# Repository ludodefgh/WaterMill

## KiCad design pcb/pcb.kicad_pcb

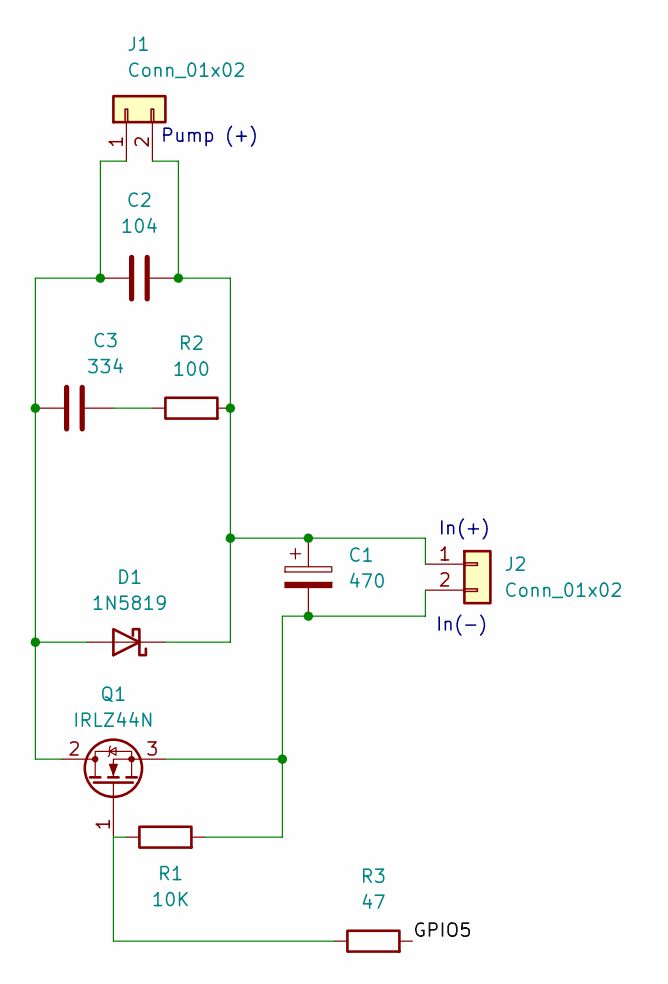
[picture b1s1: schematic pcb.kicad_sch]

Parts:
C1: 470; CP_Radial_D8.0mm_P3.50mm
C2: 104; C_Disc_D5.0mm_W2.5mm_P2.50mm
C3: 334; C_Disc_D5.0mm_W2.5mm_P2.50mm
D1: 1N5819; D_DO-41_SOD81_P10.16mm_Horizontal
J1, J2: Conn_01x02; JST_PH_B2B-PH-K_1x02_P2.00mm_Vertical
Q1: IRLZ44N; TO-220-3_Vertical
R1: 10K; R_Axial_DIN0207_L6.3mm_D2.5mm_P10.16mm_Horizontal
R2: 100; R_Axial_DIN0207_L6.3mm_D2.5mm_P10.16mm_Horizontal
R3: 47; R_Axial_DIN0207_L6.3mm_D2.5mm_P10.16mm_Horizontal

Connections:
/GPIO5: R3.2
unnamed: C3.2, R2.1
unnamed: C2.1, C3.1, D1.2 (A), J1.1, Q1.2 (D)
unnamed: C1.1, C2.2, D1.1 (K), J1.2, J2.1, R2.2
unnamed: C1.2, J2.2, Q1.3 (S), R1.2
unnamed: Q1.1 (G), R1.1, R3.1

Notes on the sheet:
Pump (+)
In(-)
In(+)

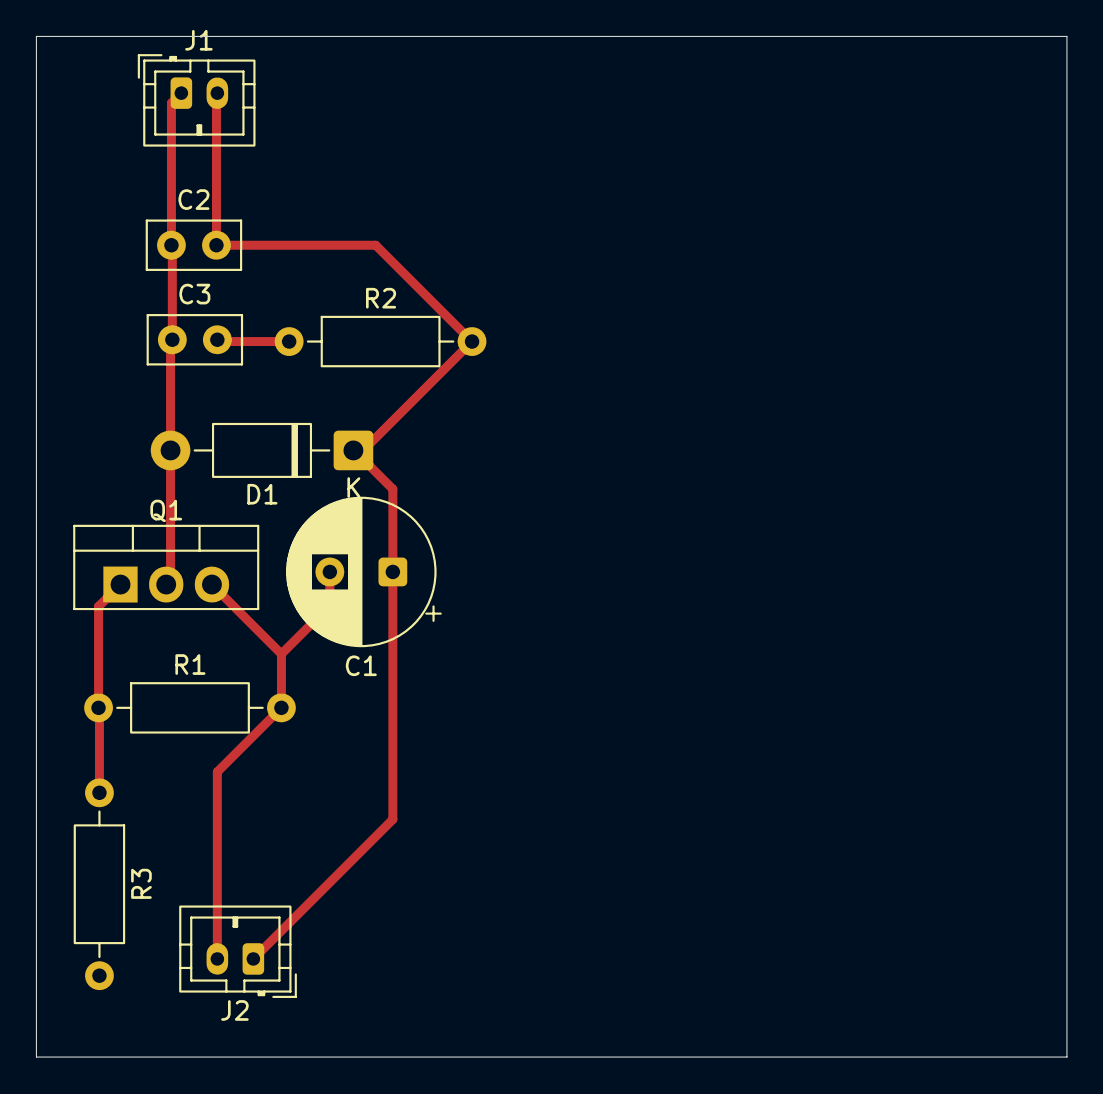
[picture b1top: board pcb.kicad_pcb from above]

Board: 2 copper layers, 57.2 x 56.7 mm, 10 parts (0 on the bottom side), 5 nets.
